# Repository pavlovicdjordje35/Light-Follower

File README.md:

# Light-Follower

<picture>
  <source media="(prefers-color-scheme: dark)" srcset="Final.png">
  <source media="(prefers-color-scheme: light)" srcset="Final.png">
  
</picture>

<picture>
  <source media="(prefers-color-scheme: dark)" srcset="PCB.png">
  <source media="(prefers-color-scheme: light)" srcset="PCB.png">
  
</picture>

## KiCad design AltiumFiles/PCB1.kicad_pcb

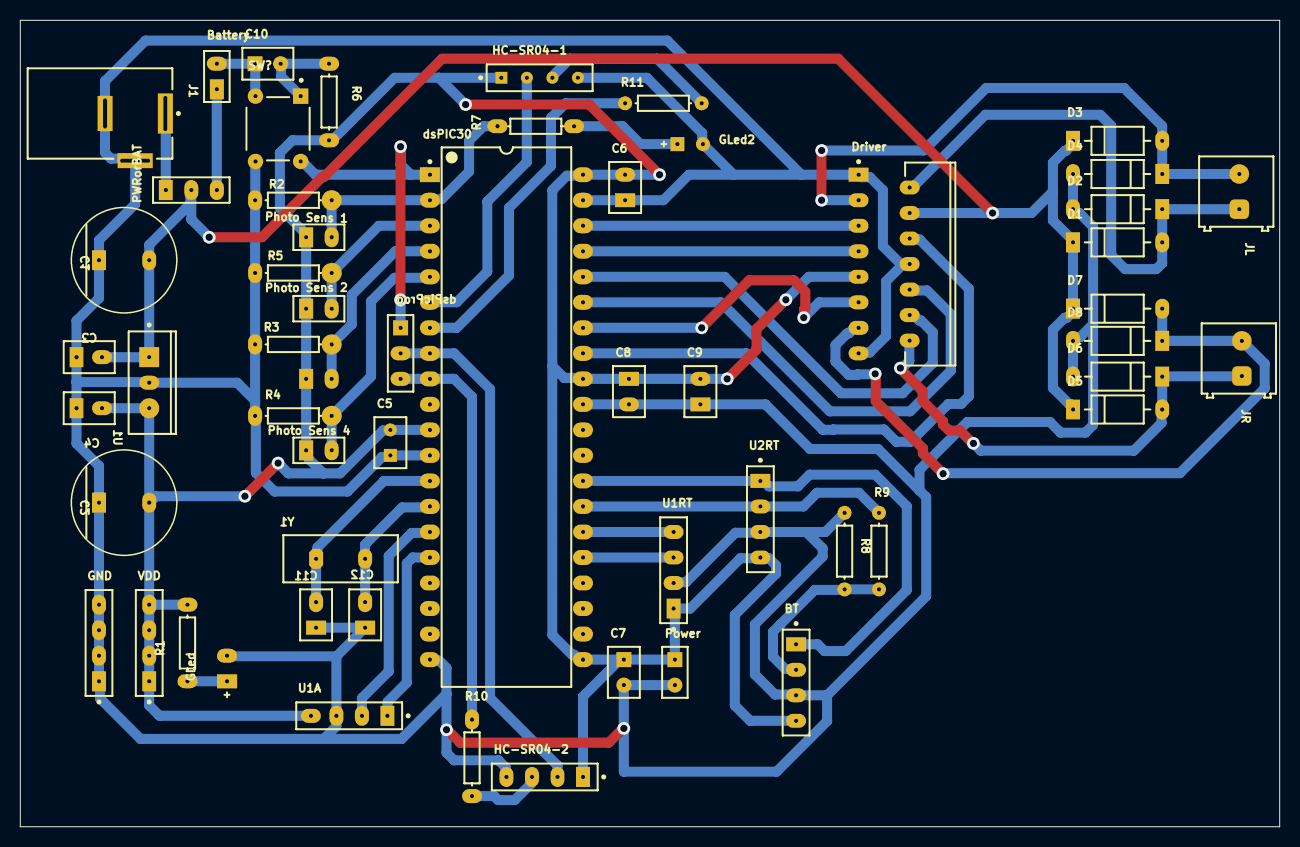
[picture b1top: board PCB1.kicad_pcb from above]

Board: 2 copper layers, 125.3 x 80.3 mm, 57 parts (1 on the bottom side), 37 nets.

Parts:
BT: SS-104-G-2; FP-SS-104-G-2-MFG
Battery: Header 2; HDR1X2
C1, C2: EEUHD1H471B; FP-RAD-TH-D_10_0_5-L_20_2-MFG
C3, C4, C5, C6, C7, C8, C9, C10, C11, C12: C320C104K5R5TA; CAPR51-254-508X318X736
D1, D2, D3, D4, D5, D6, D7, D8: 1N4007; FP-1N4007-MFG
Driver: L298N; STM-FM-15
GLed, GLed2: LTL-1CHG; LTST-LTL-1CHG-2
GND: SS-104-G-2; FP-SS-104-G-2-MFG
HC-SR04-1, HC-SR04-2: SS-104-G-2; FP-SS-104-G-2-MFG
J1: PJ-002A; CUI-PJ-002A_V
JL: 691214110002
JR: 691214110002
PWRorBAT: Header 3; HDR1X3
Photo Sens 1, Photo Sens 2, Photo Sens 3, Photo Sens 4: Header 2; HDR1X2
Power: Header 2; HDR1X2
R1, R2, R3, R4, R5, R6, R7, R8, R9, R10, R11: Res1; AXIAL-0.3
SW?: 2-1825910-7; FP-2-1825910-7-MFG
U1: LM7805CT; FAIR-TO-220-3
U1A, U1RT, U2RT: SS-104-G-2; FP-SS-104-G-2-MFG
VDD: SS-104-G-2; FP-SS-104-G-2-MFG
Y1: ECS-100-18-1; HC-49U
dsPIC30: DSPIC30F4013-20E/P; PDIP600-P40
dsPicProg: Header 3; HDR1X3

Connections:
GND: BT.3, Battery.2, C1.1, C2.1, C3.1, C4.1, C5.1, C6.1, C7.2, C8.2, C9.1, C10.1, C11.1, C12.1, D2.2, D4.2, D6.2, D8.2, Driver.1, Driver.8, Driver.15, GLed.2, GLed2.2, GND.1, GND.2, GND.3, GND.4, HC-SR04-1.4, HC-SR04-2.4, J1.2, J1.3, Power.2, R2.1, R3.1, R4.2, R5.2, R8.2, SW?.3, SW?.4, U1.2, U1A.3, U1RT.2, U2RT.3, dsPIC30.12, dsPIC30.20, dsPIC30.31, dsPIC30.39
MCLR: C10.2, R6.1, SW?.1, SW?.2, dsPIC30.1, dsPicProg.1
NetBT_2: BT.2, R8.1, R9.1
NetD1_2: D1.2, D2.1, Driver.2, JL.1
NetD3_2: D3.2, D4.1, Driver.3, JL.2
NetD5_2: D5.2, D6.1, Driver.14, JR.1
NetD7_2: D7.2, D8.1, Driver.13, JR.2
NetGLed2_1: GLed2.1, R7.1
NetGLed_1: GLed.1, R1.1
NetHC-SR04-1_3: HC-SR04-1.3, R11.2
NetHC-SR04-2_3: HC-SR04-2.3, R10.2
OSC1: C11.2, Y1.1, dsPIC30.13
PGC: HC-SR04-2.2, dsPIC30.8, dsPicProg.2
PGD: R10.1, dsPIC30.9, dsPicProg.3
RB0: Photo Sens 1.2, R2.2, R7.2, dsPIC30.2
RB1: Photo Sens 2.2, R5.1, dsPIC30.3
RB2: Photo Sens 3.2, R3.2, dsPIC30.4
RB3: Photo Sens 4.2, R4.1, dsPIC30.5
RB4: HC-SR04-1.2, dsPIC30.6
RB5: R11.1, dsPIC30.7
RB9: Driver.5, dsPIC30.38
RB10: Driver.7, dsPIC30.37
RB11: Driver.12, dsPIC30.36
RB12: Driver.10, dsPIC30.35
RC13: U1A.2, dsPIC30.15
RC14: U1A.1, dsPIC30.16
RC15: C12.2, Y1.2, dsPIC30.14
RD0: Driver.11, dsPIC30.34
RD1: Driver.6, dsPIC30.33
RF2: U1RT.4, dsPIC30.26
RF3: U1RT.3, dsPIC30.25
RF4: BT.1, U2RT.1, dsPIC30.28
RF5: R9.2, U2RT.2, dsPIC30.27
VCC: C1.2, C3.2, D1.1, D3.1, D5.1, D7.1, Driver.4, PWRorBAT.2, U1.1
Vbat: Battery.1, PWRorBAT.3
Vdd: BT.4, C2.2, C4.2, C5.2, C6.2, C7.1, C8.1, C9.2, Driver.9, HC-SR04-1.1, HC-SR04-2.1, Photo Sens 1.1, Photo Sens 2.1, Photo Sens 3.1, Photo Sens 4.1, Power.1, R1.2, R6.2, U1.3, U1A.4, U1RT.1, U2RT.4, VDD.1, VDD.2, VDD.3, VDD.4, dsPIC30.11, dsPIC30.21, dsPIC30.32, dsPIC30.40
Vpwr: J1.1, PWRorBAT.1

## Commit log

2024-01-27 Skoro gotova verzija
2024-01-29 DONE PCB
2024-02-02 slika pcb-a
2024-02-14 Gotova verzija
2024-03-04 vreme za kod
2024-03-12 dodatak
2024-03-18 Calc() fixed
2024-03-18 Fixed Calc() again
2024-04-03 Kod za main
